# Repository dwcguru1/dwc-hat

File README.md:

# Rasperry Pi - DWC HAT

Picture above shows V3.0 - New version has some changes (e.g. pinheaders for I2C and 1-wire):

The DWC Hat does following:

- PH measurement (DWC)
- EC measurement (DWC)
- Temperature measurement and correction (DWC)
- Pressure* measurement for water level monitoring (DWC)
- Temperature and humidity measurement of air

*: Everything except the pressure sensing works as expected. It works electrically, but there would be needed a much more sophisticated temperature compensation. To sum it up: It never worked well.

## Raspberry prerequisites

Use `raspi-config` to enable I2C and 1-Wire.

There is a special quirk needed for getting the I2C working properly (because the Pi can't do clock-stretching):

In `/boot/config.txt`:

```
# Uncomment some or all of these to enable the optional hardware interfaces
dtparam=i2c_baudrate=10000
```

It hurts a bit to reduce the I2C rate to 10kHz - but it doesn't really matter :shrug:

Also, the 1-wire pin needs to be configured:
```
# select 1-wire pin
dtoverlay=w1-gpio,gpiopin=4,pullup=on
```

## I2C and 1-wire Devices

There are four I2C and one 1-wire device.

### I2C

```
i2cdetect -y 1:

     0  1  2  3  4  5  6  7  8  9  a  b  c  d  e  f
00:          -- -- -- -- -- -- -- -- -- -- -- -- -- 
10: 10 -- -- -- -- -- -- -- -- -- -- -- -- -- -- -- 
20: -- -- -- -- -- -- -- -- -- -- -- -- -- -- -- -- 
30: -- -- -- -- -- -- -- -- -- -- -- -- -- -- -- -- 
40: 40 -- -- -- -- -- -- -- -- -- -- -- -- 4d -- -- 
50: -- -- -- -- -- -- -- -- -- -- -- -- -- -- -- -- 
60: -- -- -- -- -- -- -- -- -- -- 6a -- -- -- -- -- 
70: -- -- -- -- -- -- -- -- 
```

0x10: EC measurement (fixed by AVR firmware)
0x40: SI7021 temperature and humidity sensor
0x4d: MPX2050DP pressure sensor (ADC MCP3221)
0x6a: PH measurement (ADC MCP3421)

The addresses can differ (e.g. the ADC used in the PH measurement could be either of 0x68 to 0x6f). 

Please check the datasheets of the parts mentioned above and/or `i2cdetect` for the address of your part.

The values are inserted into the `config.ini`:
```
[i2c]
# i2c address of EC measuring (always 0x10)
i2c_ec = 0x10

# i2c address of PH measuring
i2c_ph = 0x6a

# i2c address of MPX2050DP
i2c_pressure = 0x4d

# i2c address of SI7021
i2c_ht = 0x40
```

# 1-Wire

After connecting the 1-wire sensor, there should appear a new device at `/sys/bus/w1/devices/`. 

Add the name to the `config.ini`:

```
[1wire]
ds18b20 = "28-0120625ed8f9"
```

## AVR firmware

The EC-measuring part uses an AVR. Before doing measurements, it needs to be flashed with the firmware.

The ISP connector is 2x10 with 1.27mm pitch. The pinout is compatible to the USBASP.

Also the Makefile expects the USBASP as programmer.

For compilation, you'll need:

```
sudo apt install gcc-avr avrdude avr-libc
```

After that, first initialize the AVR-flags once with:
```
make fuse
```

Afterwards you can compile and flash the AVR with:
```
make
make flash
```

Now, it should be ready to go :slight_smile:

## Calibration

There are two parts that need calibration. (See usage how to get the raw-values).

### PH calibration

PH calibration is done by setting up two reference solutions with PH of 4.01 and 6.86.

After measuring the raw-values, insert them into the `config.ini`:
```
[ph]
# measured PH (raw values)
PH_401 =  13010.0
PH_686 =  2400.0
```

### EC calibration

For calibrating the EC part, two resistors are needed.

They are simply connected to the BNC jack for the EC probe (without the probe) and the raw-values measured by the EC measuring circuit is used for calculating the EC.

The resistors are  390R and 1k.

The values have to be inserted into the `config.ini`:
```
[ec]
# measured EC (raw values)
EC_ADC_390R = 439.0
EC_ADC_1K = 208.0
```

## Usage

By default, the python code does a single measurement and transmitts the date to InfluxDB.

To run it in a loop simply start it in a `screen` session with:
```
 while ((1)); do python3 read.py | tee -a measurements.log ; sleep 1; done

time=1635402997671, ec_raw=243.3764705882353, ec=1345.546146, ph_raw=6772, ph=5.685617, temp=20.875000, pressure_raw=122.5625, pressure_comp=44.20985378262856, humidity=68.68032836914062, airtemp=22.873859863281247
...
```

### Grafana and InfluxDB

Follow any tutorial for installing InfluxDB and Grafana.

Default Database, User, Password is in the `config.ini`.

Make sure to configure the timezone right on the Raspi.

## TODO

There are some things I would like to improve:

- STM32 (M4) for EC measurement. Use internal DAC for DDS sine generation and FIR band pass. This would reduce the parts needed by a lot. Also would improve resolution (12Bit ADC instead of 10Bit ADC).
- Better pt1000 based temperature sensor for DWC. DS18B20 digitizes too coarse what affects temperature compensation of EC negatively.
- Replace the pressure sensing with something else better working. E.g. capacitive sensing with conductive strips glued on the outside of the DWC bin or something else ...

## Disclaimer

Use everything on your own risk!

The project is at it is and if I don't need something else, I won't touch it ever again.

Feel free to do with it whatever you like :slight_smile:

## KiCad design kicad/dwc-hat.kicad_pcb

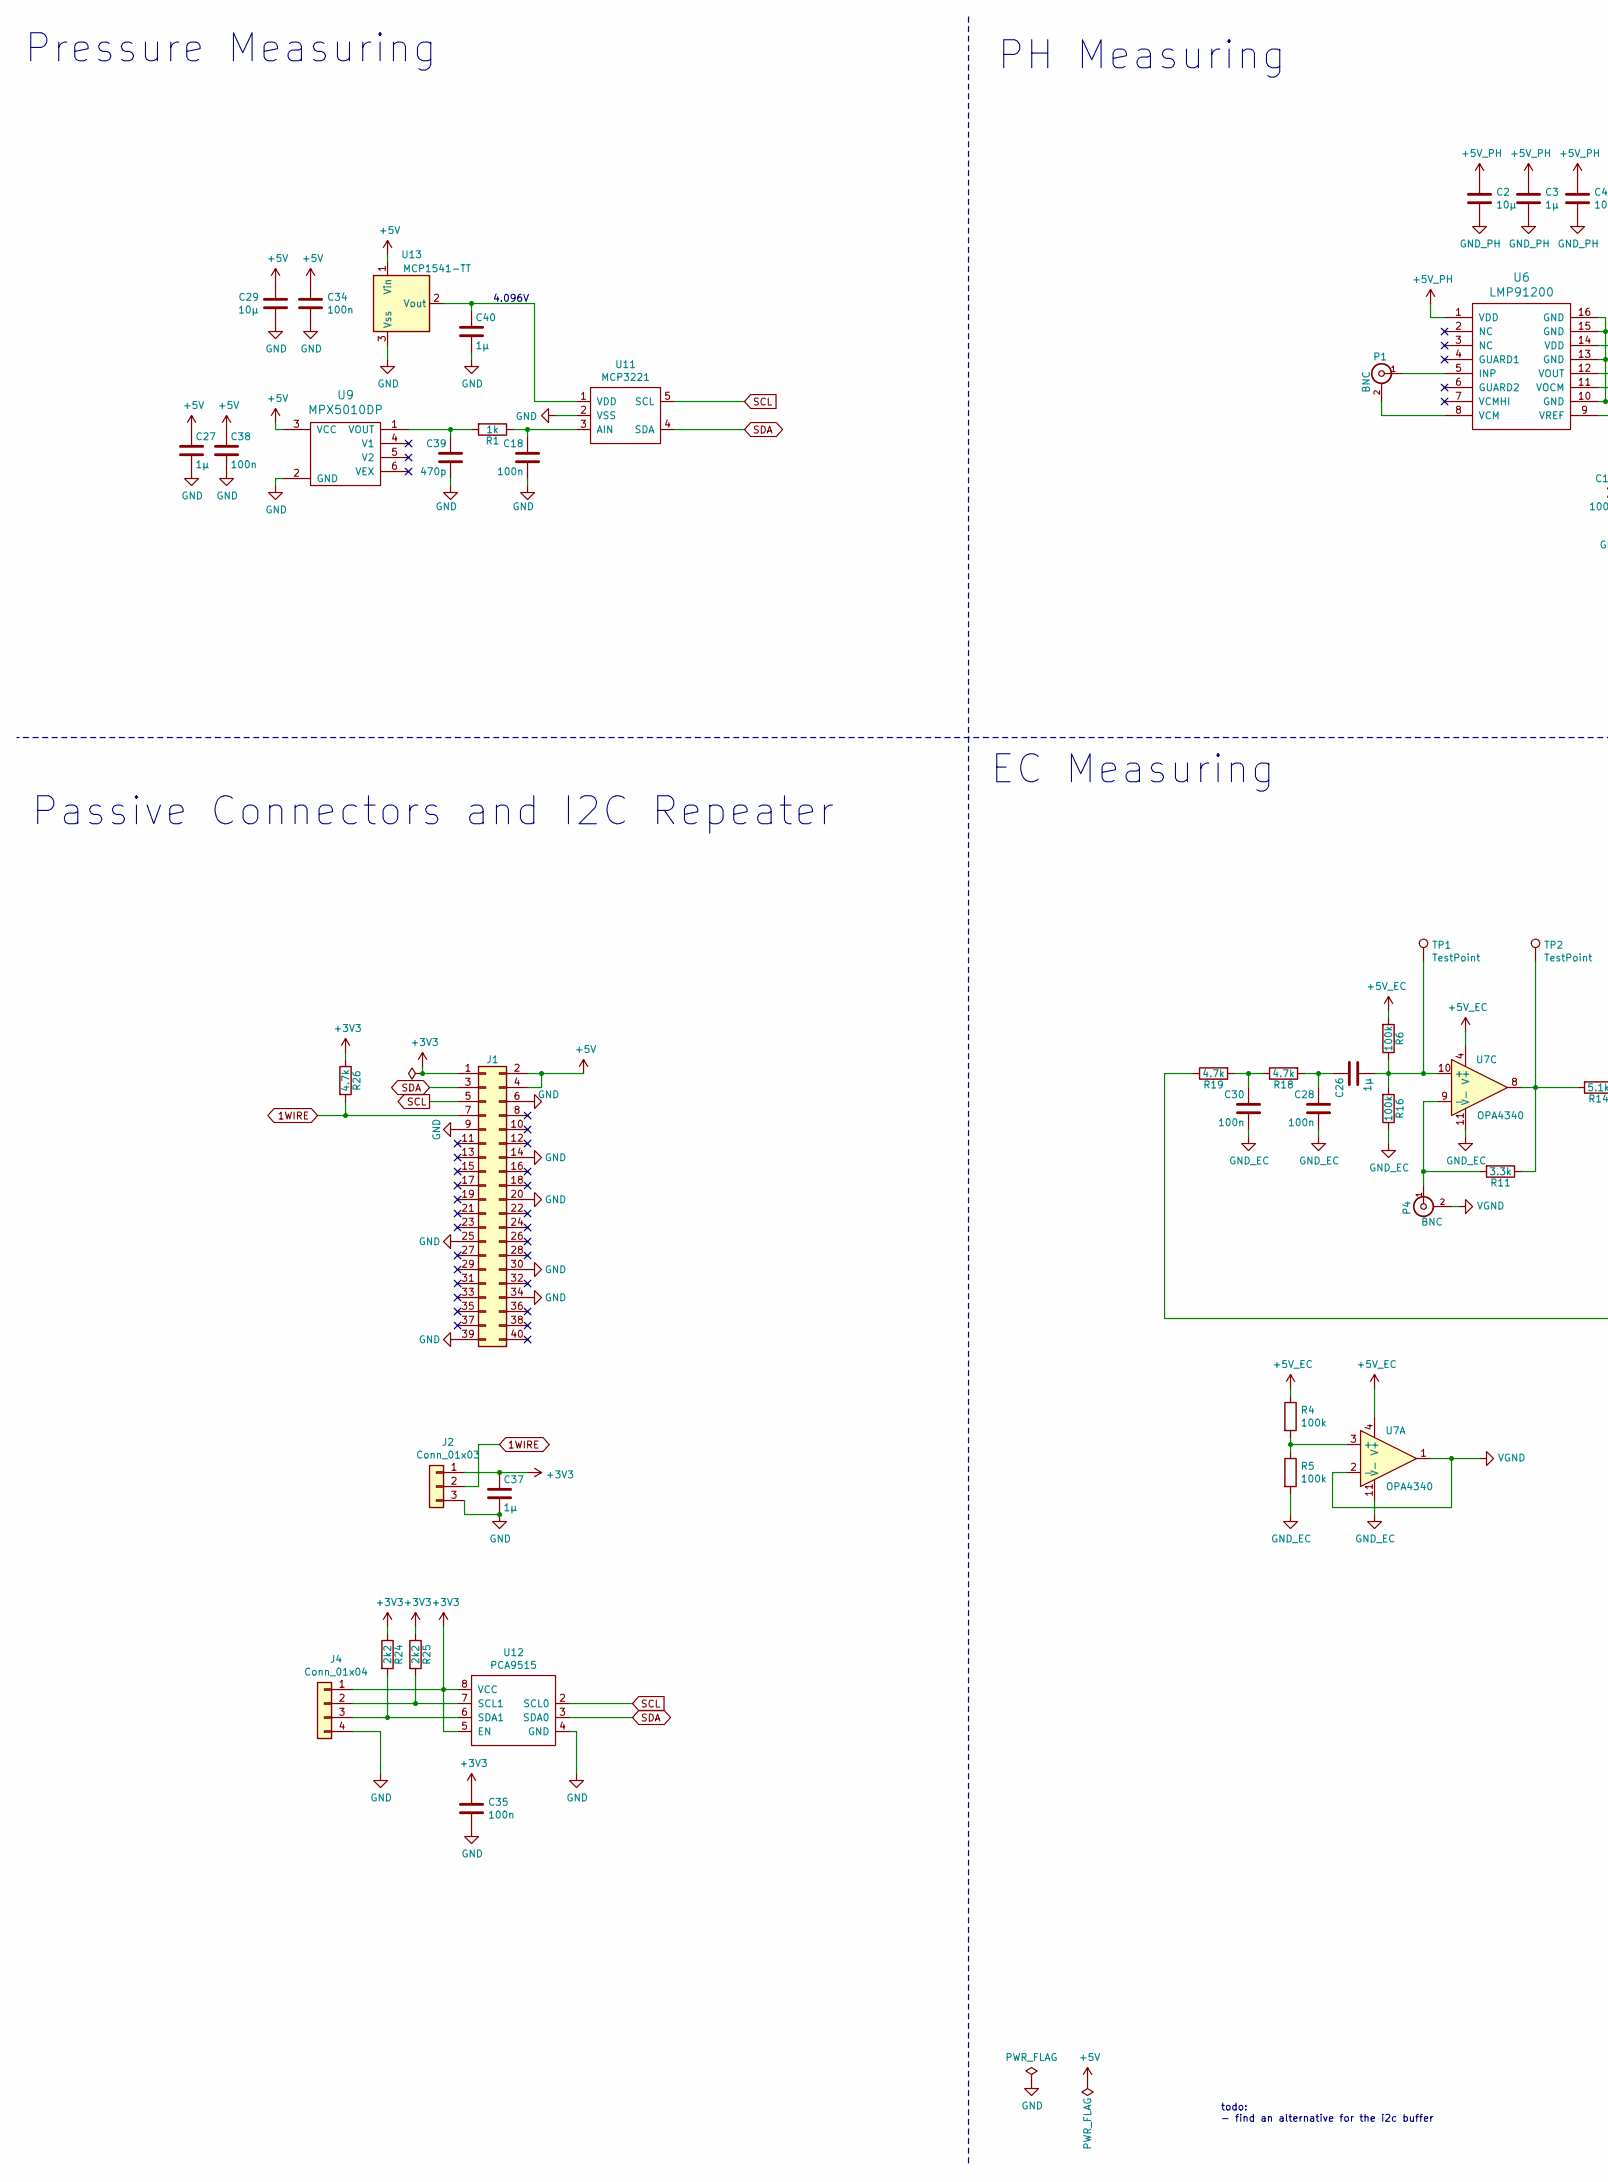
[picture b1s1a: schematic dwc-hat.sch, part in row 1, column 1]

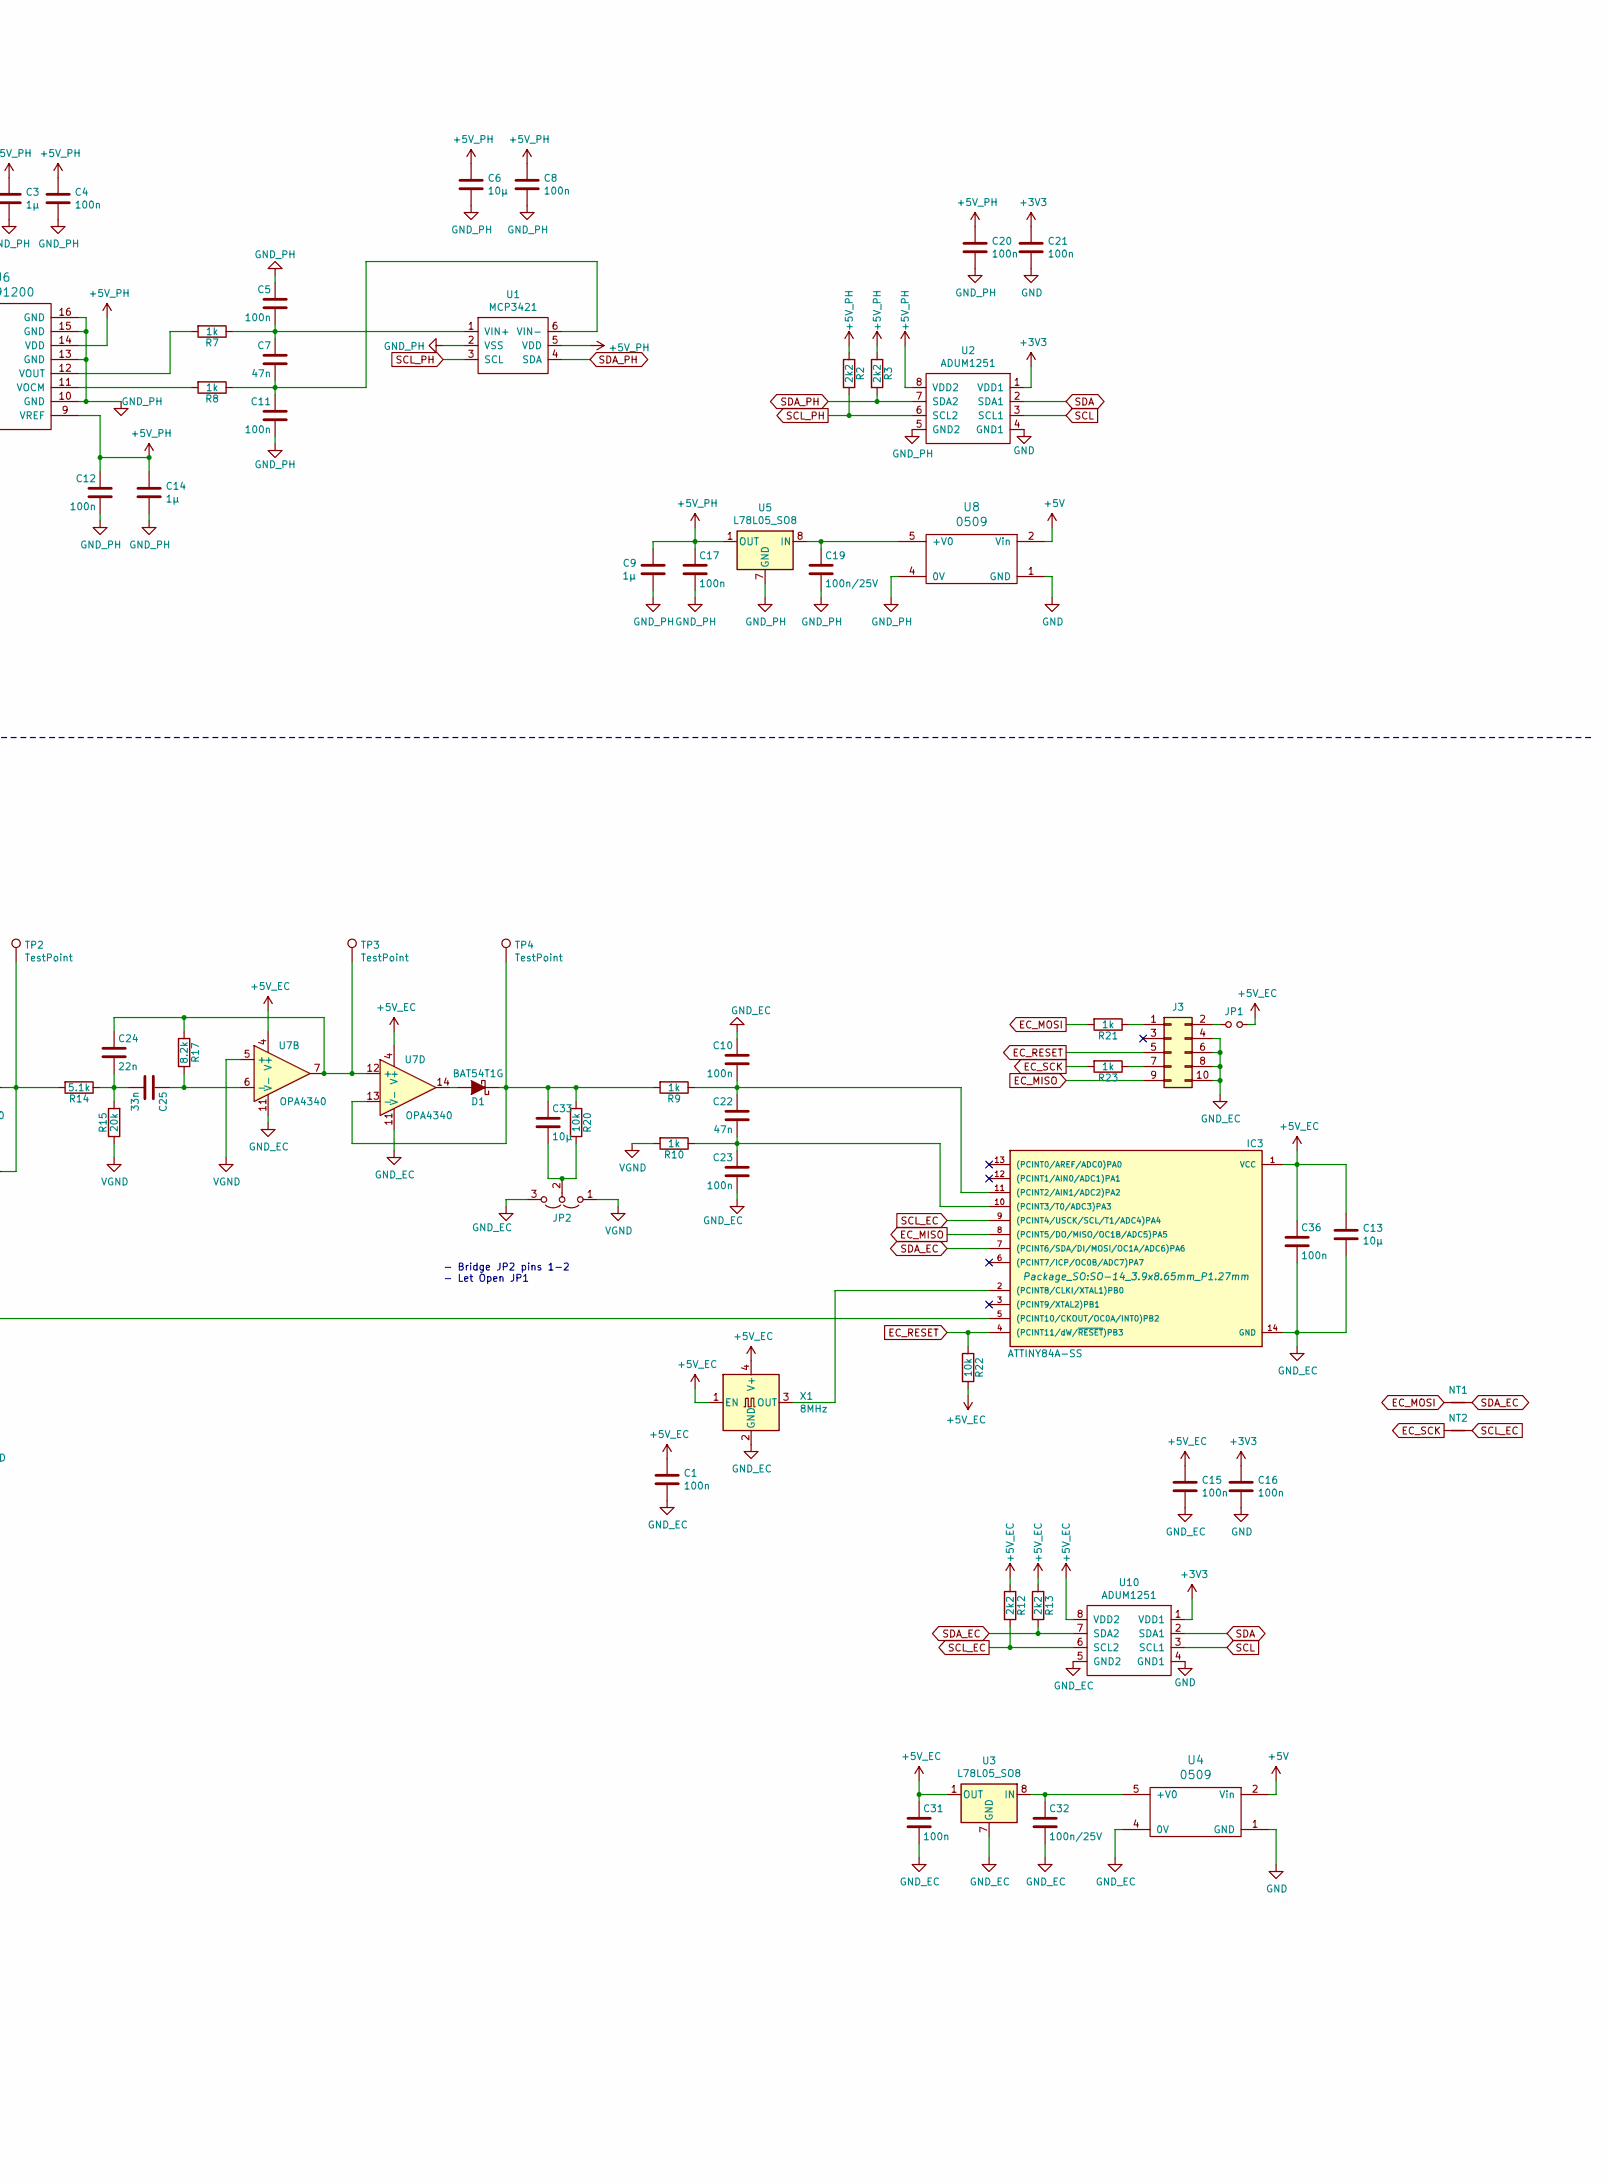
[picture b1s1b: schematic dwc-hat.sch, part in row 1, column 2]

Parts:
C1, C4, C5, C8, C10, C11, C12, C15, C16, C17, C18, C20, C21, C23, C28, C30, C31, C34, C35, C36, C38: 100n; C_0805_2012Metric
C2, C6, C13, C29, C33: 10µ; C_1206_3216Metric
C3, C9, C14, C26, C27, C37, C40: 1µ; C_0805_2012Metric
C7, C22: 47n; C_0805_2012Metric
C19, C32: 100n/25V; C_0805_2012Metric
C24: 22n; C_0805_2012Metric
C25: 33n; C_0805_2012Metric
C39: 470p; C_0805_2012Metric
D1: BAT54T1G; SOD-123
IC3: ATTINY84A-SS; SO-14_3.9x8.65mm_P1.27mm
J1: Raspberry Pi GPIO; PinSocket_2x20_P2.54mm_Vertical
J2: Conn_01x03; PinHeader_1x03_P2.54mm_Vertical
J3: Conn_02x05_Odd_Even; PinHeader_IDC_2x05_P1.27mm_Vertical_SMD
J4: Conn_01x04; PinHeader_1x04_P2.54mm_Vertical
JP1: Jumper_NO_Small; SolderJumper-2_P1.3mm_Open_RoundedPad1.0x1.5mm
JP2: Jumper_3_Open; SolderJumper-3_P1.3mm_Open_RoundedPad1.0x1.5mm
NT1, NT2: Net-Tie_2; NetTie-2_SMD_Pad0.5mm
P1, P4: BNC; BNC_UG_1094W1
R1, R7, R8, R9, R10, R21, R23: 1k; R_0805_2012Metric
R2, R3, R12, R13, R24, R25: 2k2; R_0805_2012Metric
R4, R5, R6, R16: 100k; R_0805_2012Metric
R11: 3.3k; R_0805_2012Metric
R14: 5.1k; R_0805_2012Metric
R15: 20k; R_0805_2012Metric
R17: 8.2k; R_0805_2012Metric
R18, R19, R26: 4.7k; R_0805_2012Metric
R20, R22: 10k; R_0805_2012Metric
TP1, TP2, TP3, TP4: TestPoint; TestPoint_Pad_1.5x1.5mm
U1: MCP3421; SOT-23-6
U2, U10: ADUM1251; SOIC-8_3.9x4.9mm_P1.27mm
U3, U5: L78L05_SO8; SOIC-8_3.9x4.9mm_P1.27mm
U4, U8: 0509; Converter_DCDC_SMD
U6: LMP91200; TSSOP-16_4.4x5mm_P0.65mm
U7: OPA4340; SO-14_3.9x8.65mm_P1.27mm
U9: MPX5010DP
U11: MCP3221; SOT-23-5
U12: PCA9515; SO-8_3.9x4.9mm_P1.27mm
U13: MCP1541-TT; SOT-23
X1: 8MHz; Oscillator_SMD_EuroQuartz_XO32-4Pin_3.2x2.5mm

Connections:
1WIRE: J1.7, J2.2, R26.2
+3V3: C16.1, C21.1, C35.1, C37.1, J1.1, J2.1, J4.1, R24.1, R25.1, R26.1, U2.1 (VDD1), U10.1 (VDD1), U12.5 (EN), U12.8 (VCC)
+5V: C27.1, C29.1, C34.1, C38.1, J1.2, J1.4, U4.2 (Vin), U8.2 (Vin), U9.3 (VCC), U13.1 (Vin)
+5V_EC: C1.1, C13.1, C15.1, C31.1, C36.1, IC3.1 (VCC), JP1.2, R4.1, R6.2, R12.1, R13.1, R22.2, U3.1 (OUT), U7.4 (V+), U10.8 (VDD2), X1.1 (EN), X1.4 (V+)
+5V_PH: C2.1, C3.1, C4.1, C6.1, C8.1, C9.1, C12.1, C14.1, C17.1, C20.1, R2.1, R3.1, U1.5 (VDD), U2.8 (VDD2), U5.1 (OUT), U6.1 (VDD), U6.9 (VREF), U6.14 (VDD)
EC_MISO: IC3.8 ((PCINT5/DO/MISO/OC1B/ADC5)PA5), J3.9
EC_MOSI: NT1.1, R21.2
EC_RESET: IC3.4 ((PCINT11/dW/~RESET~)PB3), J3.5, R22.1
EC_SCK: NT2.1, R23.2
GND: C16.2, C18.2, C21.2, C27.2, C29.2, C34.2, C35.2, C37.2, C38.2, C39.2, C40.2, J1.6, J1.9, J1.14, J1.20, J1.25, J1.30, J1.34, J1.39, J2.3, J4.4, U2.4 (GND1), U4.1 (GND), U8.1 (GND), U9.2 (GND), U10.4 (GND1), U11.2 (VSS), U12.4 (GND), U13.3 (Vss)
GND_EC: C1.2, C10.1, C13.2, C15.2, C23.2, C28.2, C30.2, C31.2, C32.2, C36.2, IC3.14 (GND), J3.4, J3.6, J3.8, J3.10, JP2.3 (B), R5.2, R16.1, U3.2 (GND), U3.3 (GND), U3.6 (GND), U3.7 (GND), U4.4 (0V), U7.11 (V-), U10.5 (GND2), X1.2 (GND)
GND_PH: C2.2, C3.2, C4.2, C5.1, C6.2, C8.2, C9.2, C11.2, C12.2, C14.2, C17.2, C19.2, C20.2, U1.2 (VSS), U2.5 (GND2), U5.2 (GND), U5.3 (GND), U5.6 (GND), U5.7 (GND), U6.10 (GND), U6.13 (GND), U6.15 (GND), U6.16 (GND), U8.4 (0V)
unnamed: C5.2, C7.1, R7.1, U1.1 (VIN+)
unnamed: C10.2, C22.1, IC3.11 ((PCINT2/AIN1/ADC2)PA2), R9.1
unnamed: C7.2, C11.1, R8.1, U1.6 (VIN-)
unnamed: C18.1, R1.1, U11.3 (AIN)
unnamed: C19.1, U5.8 (IN), U8.5 (+V0)
unnamed: C22.2, C23.1, IC3.10 ((PCINT3/T0/ADC3)PA3), R10.1
unnamed: C24.1, R17.1, TP3.1, U7.7, U7.12 (+)
unnamed: C24.2, C25.2, R14.1, R15.2
unnamed: C25.1, R17.2, U7.6 (-)
unnamed: C26.1, C28.1, R18.2
unnamed: C26.2, R6.1, R16.2, TP1.1, U7.10 (+)
unnamed: C30.1, R18.1, R19.2
unnamed: C32.1, U3.8 (IN), U4.5 (+V0)
unnamed: C33.1, D1.1 (K), R9.2, R20.1, TP4.1, U7.13 (-)
unnamed: C33.2, JP2.2 (C), R20.2
unnamed: C39.1, R1.2, U9.1 (VOUT)
unnamed: C40.1, U11.1 (VDD), U13.2 (Vout)
unnamed: D1.2 (A), U7.14
unnamed: IC3.2 ((PCINT8/CLKI/XTAL1)PB0), X1.3 (OUT)
unnamed: IC3.5 ((PCINT10/CKOUT/OC0A/INT0)PB2), R19.1
unnamed: J3.1, R21.1
unnamed: J3.2, JP1.1
unnamed: J3.7, R23.1
unnamed: J4.2, R25.2, U12.7 (SCL1)
unnamed: J4.3, R24.2, U12.6 (SDA1)
unnamed: P1.1 (In), U6.5 (INP)
unnamed: P1.2 (Ext), U6.8 (VCM)
unnamed: P4.1 (In), R11.2, U7.9 (-)
unnamed: R4.2, R5.1, U7.3 (+)
unnamed: R7.2, U6.12 (VOUT)
unnamed: R8.2, U6.11 (VOCM)
unnamed: R11.1, R14.2, TP2.1, U7.8
SCL: J1.5, U2.3 (SCL1), U10.3 (SCL1), U11.5 (SCL), U12.2 (SCL0)
SCL_EC: IC3.9 ((PCINT4/USCK/SCL/T1/ADC4)PA4), NT2.2, R12.2, U10.6 (SCL2)
SCL_PH: R2.2, U1.3 (SCL), U2.6 (SCL2)
SDA: J1.3, U2.2 (SDA1), U10.2 (SDA1), U11.4 (SDA), U12.3 (SDA0)
SDA_EC: IC3.7 ((PCINT6/SDA/DI/MOSI/OC1A/ADC6)PA6), NT1.2, R13.2, U10.7 (SDA2)
SDA_PH: R3.2, U1.4 (SDA), U2.7 (SDA2)
VGND: JP2.1 (A), P4.2 (Ext), R10.2, R15.1, U7.1, U7.2 (-), U7.5 (+)

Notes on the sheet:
todo: - find an alternative for the i2c buffer
EC Measuring
PH Measuring
Pressure Measuring
Passive Connectors and I2C Repeater
- Bridge JP2 pins 1-2 - Let Open JP1
4.096V

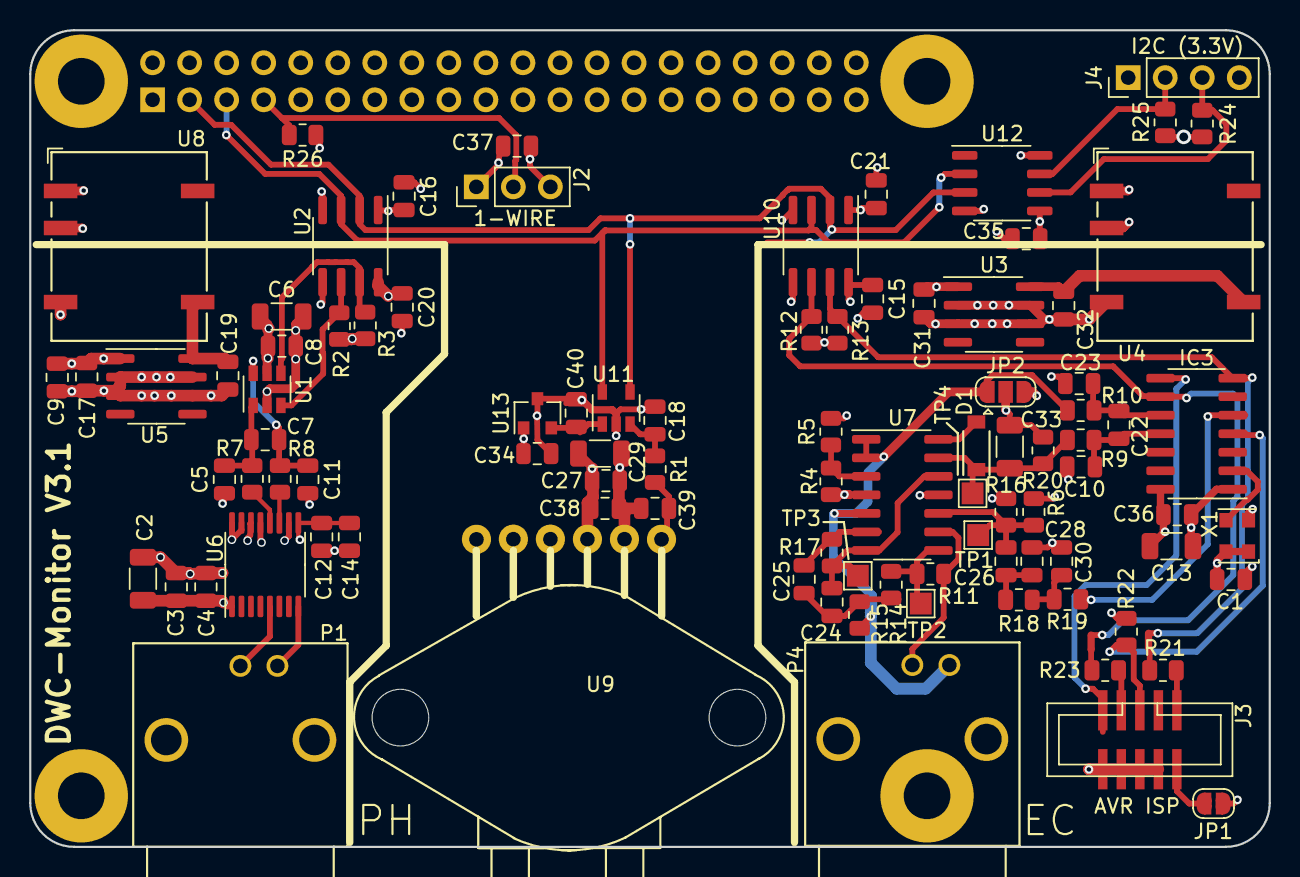
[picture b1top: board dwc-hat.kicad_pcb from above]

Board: 4 copper layers, 85.0 x 56.0 mm, 96 parts (1 on the bottom side), 51 nets.
